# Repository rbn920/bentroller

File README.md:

# Bentroller V2

PCB design for controlling the populer BentoBox air filter. The PCB uses an ESP32 to simple control of the Bentobox in Home Assistant. This project is aimed primary for when the BentoBox is used in a Bambu Labs printer due to the closed firmware.

The design goals were as follows:
- Use 24v supply from the printers PSU.
- Control the fans remoteley from Home Assistant.

## Bill of Materials (BOM)

| Qty | Item                                          | Notes                        |
| --- | --------------------------------------------- | ----------------------------------------------------------------------------------------- |
| 1   | ESP32-C3 Super Mini                           |                                                                                           |
| 1   | MP1584 voltage converter module (buck converter) | Preset to 3v is preferred but adjustable is fine.                                      |
| 1   | D4184 MOSFET Control Module                   | Found [here](https://protosupplies.com/product/d4184-mosfet-control-module/)              |
| 1   | 1N5819 Diode                                  |                                                                                           |
| 3   | 2-pin JST-HX through hole connectors          |                                                                                           |
| 4   | M2x6 SHCS                                     | These are for mounting the PCB to the BentoBox.                                           |

## Printed Parts
There are parts to print in the stl folder to mount the board to the side of the BentoBox. It is a bit hacky but it works. It gets sandwiched between the fan and duct portions of the BentoBox. Print 1 of each mouth part and 4 spacers.

## Changes from V2
I never published V1. I built it and imediatly updated it but the following is a list if changes made:
- Went from an ESP32-S2 to ESP32-C3. I had a handfull of S2 boards so I used it but changed to the C3 because I only needed 1 GPIO and it is more compact.
- Voltage input on the V1 used a screw terminal. V2 moved to a JST-HX.
- V2 makes all pins of the C3 available in case anyone decides to make on of these and comes up for a clever use for the additional pins.

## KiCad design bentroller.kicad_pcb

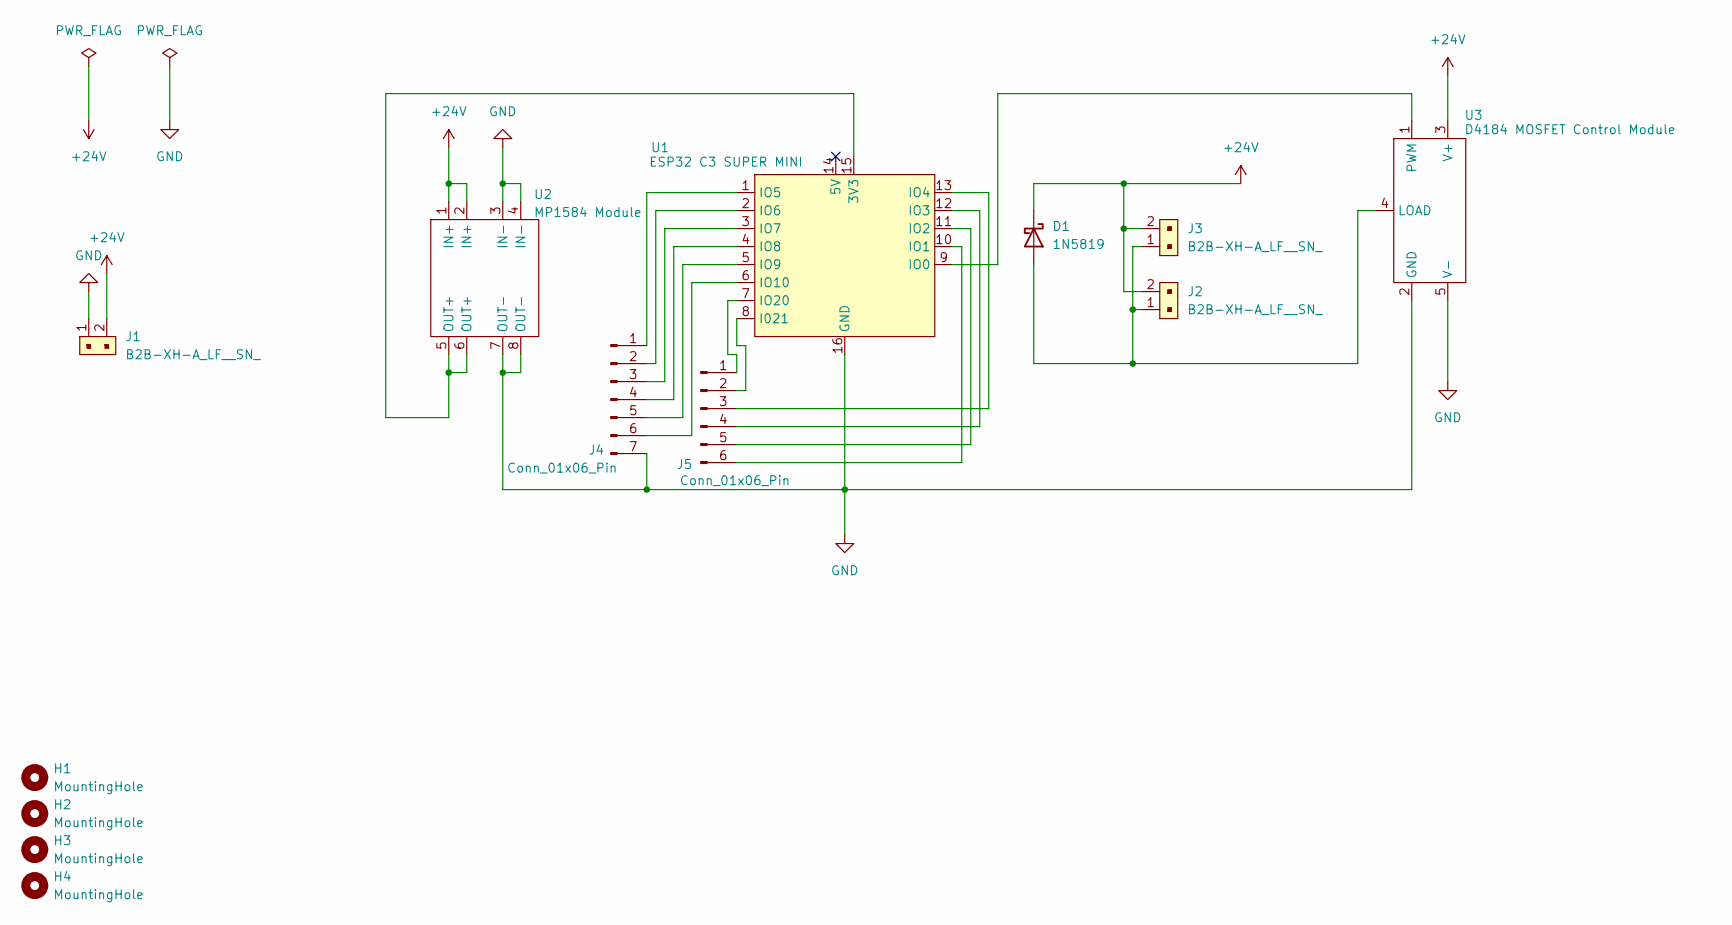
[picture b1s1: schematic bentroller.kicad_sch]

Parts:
D1: 1N5819; D_DO-41_SOD81_P10.16mm_Horizontal
H1, H2, H3, H4: MountingHole; MountingHole_2.2mm_M2
J1, J2, J3: B2B-XH-A_LF__SN_; PinHeader_1x2_P2.5mm_Drill1.1mm; MPN B2B-XH-A(LF)(SN); Digi-Key_PN 455-2247-ND
J4: Conn_01x06_Pin; PinHeader_1x07_P2.54mm_Vertical
J5: Conn_01x06_Pin; PinHeader_1x06_P2.54mm_Vertical
U1: ESP32 C3 SUPER MINI; ESP32_C3_Super_Mini
U2: MP1584 Module
U3: D4184 MOSFET Control Module

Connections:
+24V: D1.1 (K), J1.2, J2.2, J3.2, U2.1 (IN+), U2.2 (IN+), U3.3 (V+)
GND: J1.1, J4.7, U1.16 (GND), U2.3 (IN-), U2.4 (IN-), U2.7 (OUT-), U2.8 (OUT-), U3.2 (GND), U3.5 (V-)
unnamed: D1.2 (A), J2.1, J3.1, U3.4 (LOAD)
unnamed: J4.1, U1.1 (IO5)
unnamed: J4.2, U1.2 (IO6)
unnamed: J4.3, U1.3 (IO7)
unnamed: J4.4, U1.4 (IO8)
unnamed: J4.5, U1.5 (IO9)
unnamed: J4.6, U1.6 (IO10)
unnamed: J5.1, U1.7 (IO20)
unnamed: J5.2, U1.8 (I021)
unnamed: J5.3, U1.13 (IO4)
unnamed: J5.4, U1.12 (IO3)
unnamed: J5.5, U1.11 (IO2)
unnamed: J5.6, U1.10 (IO1)
unnamed: U1.15 (3V3), U2.5 (OUT+), U2.6 (OUT+)
unnamed: U1.9 (IO0), U3.1 (PWM)

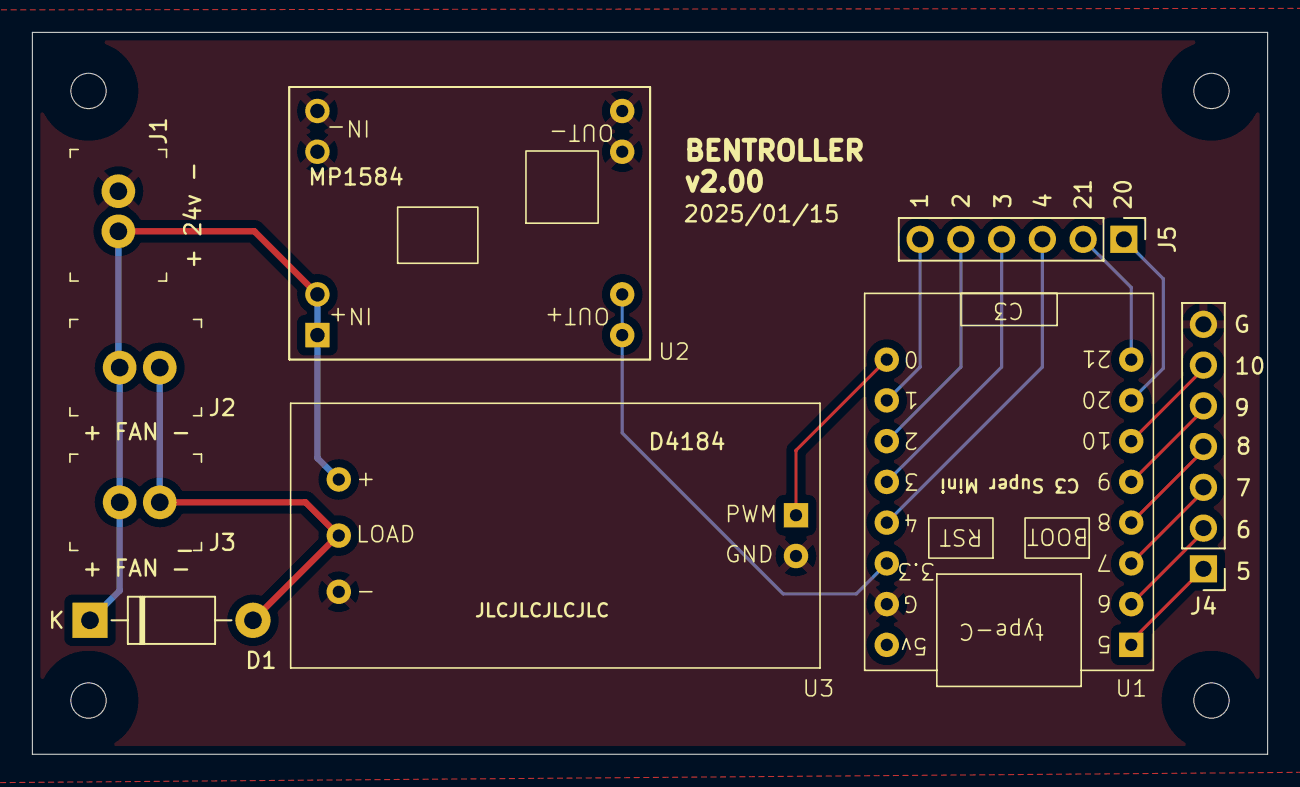
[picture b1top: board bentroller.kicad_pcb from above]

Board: 4 copper layers, 77.0 x 45.0 mm, 13 parts (0 on the bottom side), 17 nets.

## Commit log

2025-02-16 Added image
2025-02-16 Added STL files
